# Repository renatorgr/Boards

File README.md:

# Boards

Hardware and firmware for the AgOpenGPS **AiO v4.5** autosteer boards (Micro and Standard), plus section controllers for a field sprayer and a no-till seed drill. Everything here works with [AgOpenWeb](https://github.com/AgOpenGPS-Official/AgOpenWeb) and [AgOpenGPS](https://github.com/AgOpenGPS-Official/AgOpenGPS).

> [!WARNING]
> This firmware steers a tractor. Test every new version on the bench before you use it in the field. It comes with no warranty.

## What's inside

| Folder | What it is |
|---|---|
| [`Firmware/v4.5_AiO_WEB`](Firmware/v4.5_AiO_WEB) | Teensy 4.1 firmware for the AiO v4.5 Micro and Standard. Handles the GPS (UM982, F9P, X20P or dual F9P), the IMU (TM171 or BNO085) and autosteer (Cytron, IBT2, Danfoss or Keya). Has its own web page for status, settings and firmware updates over the network. |
| [`Firmware/v4.5_AiO_WEB/v4.5_XIAO_ESP32`](Firmware/v4.5_AiO_WEB/v4.5_XIAO_ESP32) | Program for a Seeed XIAO ESP32C3 or ESP32S3 on the GPS2 port. The XIAO runs its own Wi-Fi network, so you can check the module from your phone without the tablet. |
| [`Firmware/v4.5_AiO_WEB/v4.5_XIAO_ESP32_bin`](Firmware/v4.5_AiO_WEB/v4.5_XIAO_ESP32_bin) | The XIAO program, compiled and ready to install. |
| [`Firmware/simulator`](Firmware/simulator) | The web pages of the Teensy, the XIAO and the ESP32 seed drill and sprayer modules with pretend boards behind them, to try online without a board: **[renatorgr.github.io/Boards](https://renatorgr.github.io/Boards/)**. Rebuilt from the code on every change. |
| [`AiO_Micro45_XIAO_C3`](AiO_Micro45_XIAO_C3) | Adapter board (KiCad) that plugs a XIAO into the GPS2 socket of the AiO v4.5 Micro. Gerber, BOM and CPL files are ready to order from JLCPCB. |
| [`AiO_Std45_XIAO_C3`](AiO_Std45_XIAO_C3) | The same adapter for the AiO v4.5 Standard. |
| [`LED_Bezel`](LED_Bezel) | A small 3D-printed comb (OpenSCAD and STL) that slides over the three front LEDs of the AiO v4.5 so each one lights only its own window on the panel. |
| [`Relay24_ESP32`](Relay24_ESP32) | Relay board (KiCad) for an ESP32 DevKitC: 24 DPDT relays that drive 12 V linear actuators in both directions, a network socket and 12 V in, for the seed drill's sections. Gerber, BOM and CPL files for JLCPCB. |
| [`Seeder/Seeder_ESP32`](Seeder/Seeder_ESP32) | Program for the Relay24_ESP32 board (or a KinCony KC868-A32: ESP32, 32 relays, network cable) that runs the 19 sections of the no-till seed drill, one linear actuator each, on command from AgOpenWeb or AgOpenGPS (the official machine-module messages, PGN 229 for sections 17–64). Has its own web page for setup and updates. |
| [`Sprayer/Sprayer_ESP32`](Sprayer/Sprayer_ESP32) | Program for an ESP32 relay board (the ESP32_Relay_X8, or a plain ESP32 with relay modules, up to 16 relays) that runs the sprayer sections over Wi-Fi. Opens and closes the section valves on command from AgOpenWeb or AgOpenGPS (the official machine-module messages), reports boom pressure and flow, and has its own web page for setup and updates. |
| [`Sprayer/Sprayer_Nano`](Sprayer/Sprayer_Nano) | The earlier Arduino Nano + Ethernet version of the same sprayer controller. |

Each folder has its own README with the details.

## Status

- **Teensy firmware v4.5:** runs on the bench with a UM982, F9P or X20P and a TM171 or BNO085. The dual F9P, the Keya motor and steering with a BNO085 have not been tried on a tractor yet.
- **XIAO program v4.5:** must match the Teensy firmware version.
- **Adapter boards and Relay24_ESP32:** designed and checked in KiCad, but not built or tested yet.
- **Sprayer ESP32 v0.9:** runs on the bench (page, Wi-Fi), not tested on the sprayer yet. Also builds for a plain ESP32 with relay modules (up to 16 relays). Sensor dividers use 10 kΩ and 22 kΩ resistors from a common kit. The sensors fitted are ticked on its page: with none it sends no PGN 160. The Nano version (v0.3) is kept as it was.
- **Seeder ESP32 v0.2:** the seed drill part of Sprayer ESP32 v0.8 in its own folder: 19 sections over the network cable, relay 1 = section 1 and so on, on the Relay24_ESP32 board (default) or a KC868-A32. Written from the board design and KinCony's pin list, not yet run on a board.

## Getting started

### Teensy firmware

1. **First install:** connect the Teensy over USB, open the `.hex` file from [`Firmware/v4.5_AiO_WEB`](Firmware/v4.5_AiO_WEB) in Teensy Loader, then press the button on the Teensy.
2. **Web page:** open `http://192.168.5.126/` (or `http://aio.local/`) in a browser on the same network. The third number follows the subnet set in AgOpenWeb; it can also be changed from the XIAO's WiFi page (WiFi tab → Module network). To see the page before you have a module: the [simulator](https://renatorgr.github.io/Boards/).
3. **Updates:** on the web page, go to **Firmware** and choose a new `.hex` file, or click **Install from GitHub**. The page checks this repository for new versions.

### XIAO

1. **First install:** over USB-C, using the `…_USB.bin` file for your XIAO and the [esptool-js](https://espressif.github.io/esptool-js/) web page. Step-by-step instructions are in the [`v4.5_XIAO_ESP32_bin` README](Firmware/v4.5_AiO_WEB/v4.5_XIAO_ESP32_bin).
2. Join the `XIAO-xxxx` Wi-Fi network (password `agopengps`) and open `http://192.168.4.1/`.
3. **Updates:** over Wi-Fi from the XIAO page.

### Seed drill

Choosing the board, wiring (actuators, end switches), the first upload, the setup and a bench test are in the [`Seeder_ESP32` README](Seeder/Seeder_ESP32). Its web page can be tried without the board in the [simulator](https://renatorgr.github.io/Boards/seeder/).

### Sprayer

Wiring, the first upload, the Wi-Fi setup and a bench test are in the [`Sprayer_ESP32` README](Sprayer/Sprayer_ESP32). Its web page can be tried without the board in the [simulator](https://renatorgr.github.io/Boards/sprayer/). The pressure, flow and alarms show in the [AgOpenWeb fork with the sprayer readout](https://github.com/renatorgr/AgOpenWeb). The older Nano version is in [`Sprayer_Nano`](Sprayer/Sprayer_Nano).

## Building from source

- Arduino IDE 1.8 or 2.x with **Teensyduino 1.58**.
- Board settings: Teensy 4.1, USB Type "Serial", CPU Speed 600 MHz, Optimize "Faster".
- No extra libraries needed: everything the sketch uses is in its folder or comes with Teensyduino.
- GitHub Actions compiles the Teensy firmware on every pull request. A green check means it builds. The `.hex` file is under **Artifacts** on the run's page.

## Credits and licence

This work builds on the AgOpenGPS project and its community. The full list of credits is in the [Teensy firmware README](Firmware/v4.5_AiO_WEB/README.md#credits-and-licence).

- **Teensy and XIAO firmware:** GNU General Public License v3 or later. See [`COPYING`](Firmware/v4.5_AiO_WEB/COPYING).
- **Adapter boards:** same licence as the AgOpenGPS boards they fit.

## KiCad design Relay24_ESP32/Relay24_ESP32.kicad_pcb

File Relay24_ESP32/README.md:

# Relay24_ESP32 - 24-section relay board for an ESP32 DevKitC

A 210 x 120 mm two-layer board that holds everything needed to drive 24 sections with
12 V linear actuators from AgOpenGPS / AgOpenWeb (machine module over UDP):

- an **ESP32 DevKitC V4** (38 pins) plugged into two 1x19 sockets, running
  [Seeder_ESP32](../Seeder/Seeder_ESP32) or [Sprayer_ESP32](../Sprayer/Sprayer_ESP32)
  with a board profile for this hardware (see *Firmware* below);
- **three 74HC595 shift registers + three ULN2803A** driving **24 DPDT relays**
  (HF115F/012-2ZS4, 8 A); each relay reverses one actuator: relay off = actuator pulled
  in (section closed), relay on = actuator pushed out (section open); a green LED per
  section;
- **RTL8201F + RJ45** (RMII; the PHY runs on its own 25 MHz crystal and feeds the 50 MHz
  reference clock into GPIO0) so the module can sit on the tractor network cable; Wi-Fi
  stays available;
- **12 V in** with reverse-polarity diode, TVS and bulk capacitor, **LM2596S-5.0 buck**
  to 5 V (DevKitC) and **AMS1117-3.3** for the logic and the PHY;
- the actuator power comes in on its **own terminals**, one pair of rails per relay row,
  so the 12 V for the actuators never flows through the logic supply.

Schematic: [Relay24_ESP32_schematic.pdf](Relay24_ESP32_schematic.pdf). Bottom view:
[pcb_bottom.png](pcb_bottom.png). The design has **not been built yet**; see *Before
ordering* at the end.

## Connections

All screw terminals are 5.08 mm KF301 blocks, wire openings towards the board edge.

| Terminal | Function |
|---|---|
| J1 .. J12 (top edge) | sections 1 .. 12, pin 1 = red wire, pin 2 = black wire of the actuator |
| J13 .. J24 (bottom edge) | sections 13 .. 24 (13 is under 12, 24 under 1) |
| J26, J27 (top edge, both ends) | 12 V ACT A: + and - of the actuator supply for sections 1-12 (feed from one end or both) |
| J28, J29 (bottom edge, both ends) | 12 V ACT B: same for sections 13-24 |
| J25 (right edge) | 12 V IN for the board and the relay coils (put a 2 A fuse in the wire) |
| J32 | RJ45, 100 Mbit, with magnetics and link / speed LEDs on the board |
| J33 | I2C header: 3V3, GND, SDA (GPIO15), SCL (GPIO14), with 4.7 k pull-ups |
| J34 | analog header: 3V3, GND, GPIO34, GPIO35 (0 - 3.3 V inputs) |

All grounds are common (board 12 V, actuator rails, ESP32). The relay contacts:
common 1 -> red wire, common 2 -> black wire; with the coil off the red wire is on GND
and the black wire on the actuator rail, with the coil on it is the other way round.
Swap the two wires of an actuator if it moves the wrong way.

## ESP32 pins

| Function | GPIO | Notes |
|---|---|---|
| 74HC595 data (SER) | 13 | three registers in a chain: U1 (sections 1-8) -> U2 (9-16) -> U3 (17-24) |
| 74HC595 clock (SRCLK) | 16 | |
| 74HC595 latch (RCLK) | 32 | |
| 74HC595 output enable (OE, active low) | 4 | 4.7 k pull-up: all relays off until the program drives it low |
| RTL8201F MDC / MDIO | 23 / 18 | PHY address 0 (strap resistors R32 / R36) |
| RMII TXD0 / TXD1 / TX_EN | 19 / 22 / 21 | |
| RMII RXD0 / RXD1 / CRS_DV | 25 / 26 / 27 | |
| RMII 50 MHz clock | 0 | input from the PHY (`ETH_CLOCK_GPIO0_IN`), 33 ohm series resistor; quiet at boot because the PHY is in reset |
| PHY reset / power | 33 | 10 k pull-down: the PHY stays in reset until the program sets it high |
| I2C | 15 (SDA), 14 (SCL) | header J33 |
| Analog | 34, 35 | header J34, input only |

Pins 2, 5, 12 and 17 are left free. GPIO0 carries the Ethernet clock, but only once the
program releases the PHY reset on GPIO33, so the DevKitC still boots and flashes normally
(GPIO0 is the only pin the ESP32 accepts the clock on).

## Firmware

[Seeder_ESP32](../Seeder/Seeder_ESP32) v0.2 runs this board (`BOARD_RELAY24`, its
default):

- sections through the 74HC595 chain (bit 0 = section 1): 24 bits on GPIO13 / GPIO16,
  relay 24 first, latch on GPIO32; GPIO4 goes low only after the chips hold zeros;
- Ethernet: `ETH.begin(ETH_PHY_RTL8201, 0, 23, 18, 33, ETH_CLOCK_GPIO0_IN)` with
  arduino-esp32 3.x (in 2.x the order is `ETH.begin(0, 33, 23, 18, ETH_PHY_RTL8201,
  ETH_CLOCK_GPIO0_IN)`); the driver lets the PHY out of reset before it starts the
  ESP32's network block, which needs the clock. Before a restart the program puts the
  PHY back in reset;
- the DevKitC's BOOT button is not read while the network cable is in use (GPIO0 carries
  the clock); `wifi-reset` on the Serial Monitor resets a forgotten Wi-Fi password;
- the LEDs next to the relays and the PHY LEDs need no code: D30 (yellow) lights for a
  10 Mbit link, D31 (green) for 100 Mbit, the chip's default LED mode (a program can
  change it through MDIO, page 7 register 19).

## Power

- 12 V IN: board logic + relay coils, about 0.1 A idle, up to 1.1 A with all 24 coils
  on (33 mA each). Reverse-polarity diode, 18 V TVS, 100 uF.
- Actuator rails: one 12 V feed per row of 12 relays; the copper rail is 9 mm wide on
  the top layer with a second strip on the bottom layer. Feed each rail from both ends
  (J26 + J27, J28 + J29) when several actuators may move at once, or order the board
  with 2 oz copper.
- The DevKitC can be powered from USB for programming on the bench: D28 keeps the USB
  5 V out of the buck converter.

## Files

- `Relay24_ESP32.kicad_pro`, `.kicad_sch` (+ three relay sheets), `.kicad_pcb`: KiCad 7
  project. `Relay24_ESP32_schematic.pdf`, `pcb_top.png`, `pcb_bottom.png`,
  `pcb_copper_*.png`: views.
- `fabrication_JLCPCB/`: `Gerber_Relay24_ESP32.zip` (Gerber + drill), `BOM_*_all.csv` /
  `CPL_*_all.csv` (every part) and `BOM_*_smd.csv` / `CPL_*_smd.csv` (surface-mount parts
  only, for an order where the relays, terminals, sockets and RJ45 are soldered by hand).
  JLCPCB format: BOM columns *Comment, Designator, Footprint, LCSC Part #*; CPL columns
  *Designator, Mid X, Mid Y, Layer, Rotation*.
- `tools/`: the generators. `design.py` holds every part, net and position;
  `make_sch.py` writes the schematic, `make_pcb.py` places and routes the board
  (`router.py` is a small grid router for the logic signals), `make_fab.py` writes the
  JLCPCB files and the views. Run them from the project folder with the Python of
  KiCad 7 (`python3 tools/make_pcb.py .`).

## Before ordering

Things that were assumed and should be checked on the real parts:

- The DevKitC V4 sockets are 25.4 mm apart (38-pin module). Measure your module; the
  30-pin DevKitC has another pitch and does not fit.
- The RJ45 is the HanRun HR911105A pinout (pairs on 1-2 and 3-6, centre taps 4-5 and
  7-8 to 3.3 V); another jack with built-in magnetics may differ. The PHY transmit pair
  pair (MDI pair 0) is wired to pins 1-2 and the receive pair (MDI pair 1) to pins 3-6,
  the usual wiring of an end device; the RTL8201F Auto-MDIX sorts out a crossed cable.
- The RTL8201F replaced the LAN8720A on 2026-10-28 because JLCPCB assembles the LAN8720A
  only on its Standard service (setup fee, wider board). The PHY runs on a 25 MHz crystal
  and sends the reference clock out; the ESP32 reads it on GPIO0. Nothing of this has
  been built yet.
- Y1 is a 5.0 x 3.2 mm two-pin crystal (YXC X503225MSB2GI, load capacitance 20 pF, with
  33 pF from each pin to ground). JLCPCB flags the smaller 3.2 x 2.5 mm four-pin crystal
  as hard to assemble and may charge extra for it, so do not swap it back.
- The screw terminals follow the KiCad `TerminalBlock_bornier-2_P5.08mm` footprint
  (wire opening on the pin-2 side); check the orientation on the first board.
- LCSC numbers were checked against the JLCPCB parts pages on 2026-10-28; stock
  changes, so a part shown as short at order time needs an equivalent with the same
  footprint. Second-source choices: the ULN2803 is Shanghai Belling (C22437476, same
  pinout as the TI ULN2803A), the LEDs are XINGLIGHT (the "green" ones are yellow-green,
  Vf 2.2 V, low enough for the Ethernet LEDs on 3.3 V).
- L1 is the SHOU HAN CYH127-33UH (12.3 x 12.3 mm) on KiCad's `L_12x12mm_H8mm` footprint
  (pads 2.9 x 5.4 mm, 9.9 mm apart): compare with the land pattern in its datasheet.
- The references of the resistors, capacitors and LEDs are not printed on the board
  (there is no room next to the PHY); the CPL files and the schematic have them.
- The CPL gives the centre of the body for the through-hole parts (relays, terminals,
  sockets, RJ45), as JLCPCB expects, and turns the 2.54 mm sockets and headers by 90
  degrees to match JLCPCB's models. The other rotations are KiCad's; check the JLCPCB
  preview, in particular the diodes, the electrolytic capacitors, the TO-263 regulator,
  the SOT-223 and the QFN.
- Linear actuators often draw 2-3 A while moving: size the actuator supply and the fuse
  accordingly.

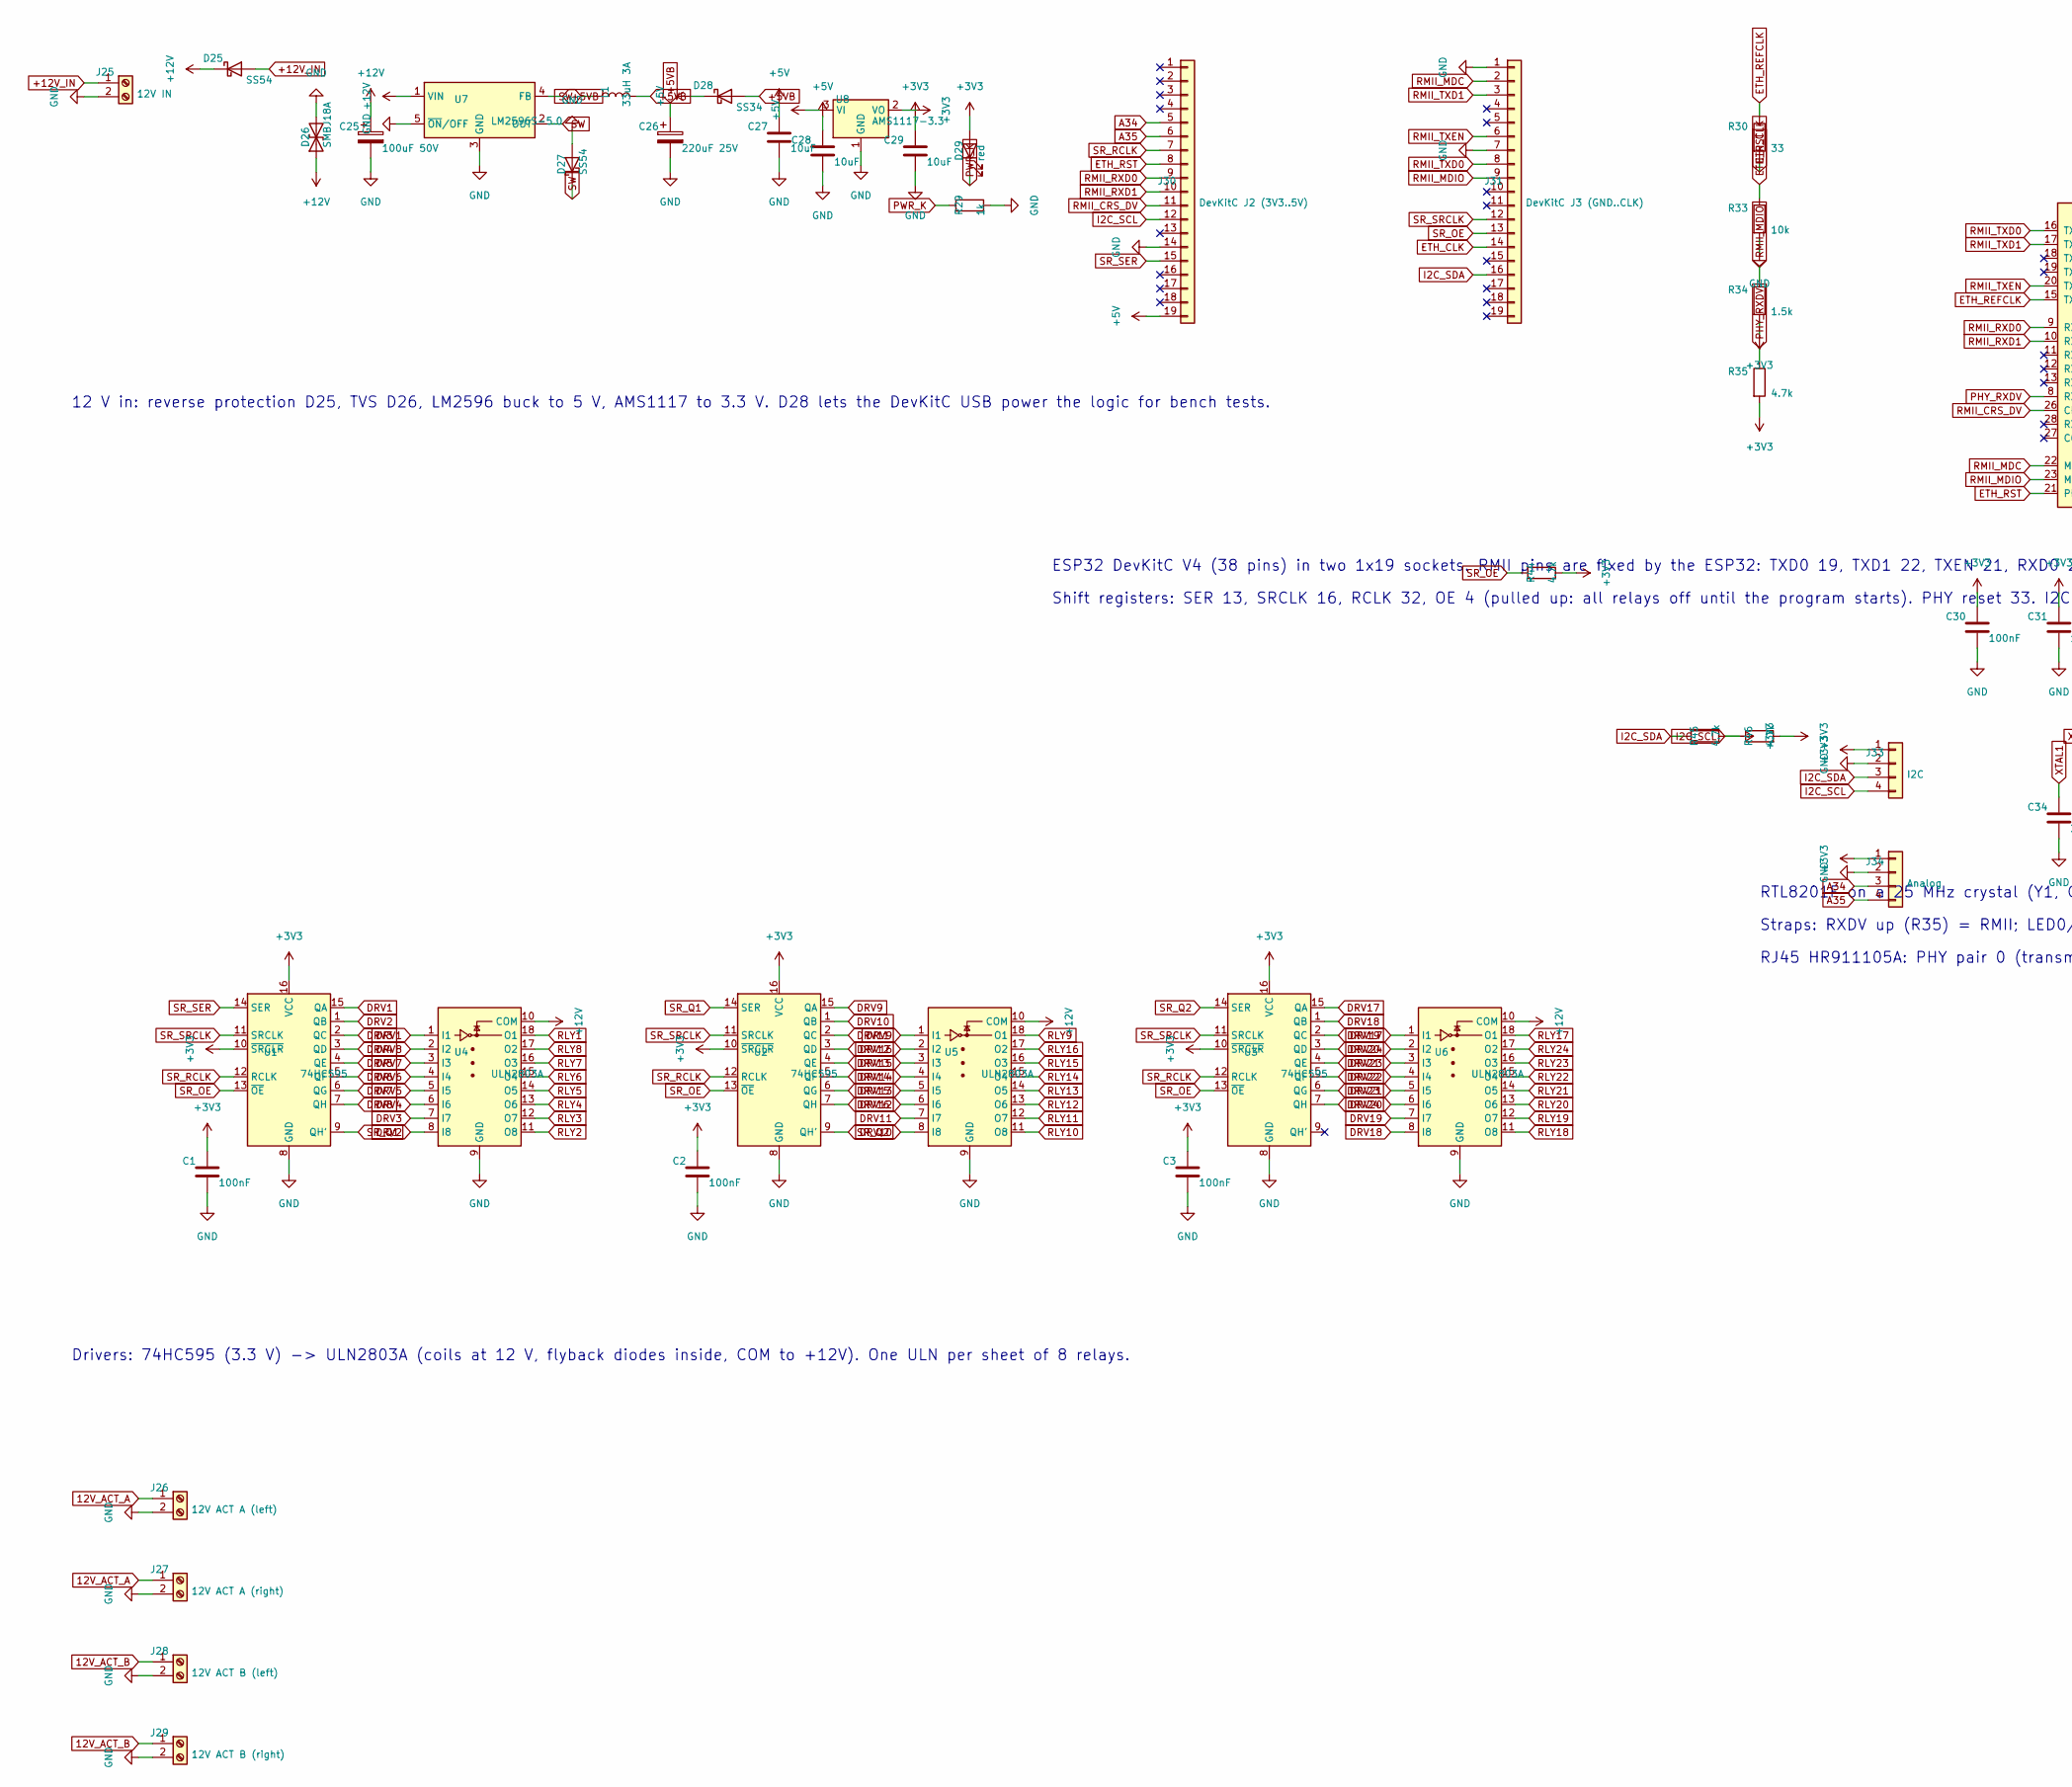
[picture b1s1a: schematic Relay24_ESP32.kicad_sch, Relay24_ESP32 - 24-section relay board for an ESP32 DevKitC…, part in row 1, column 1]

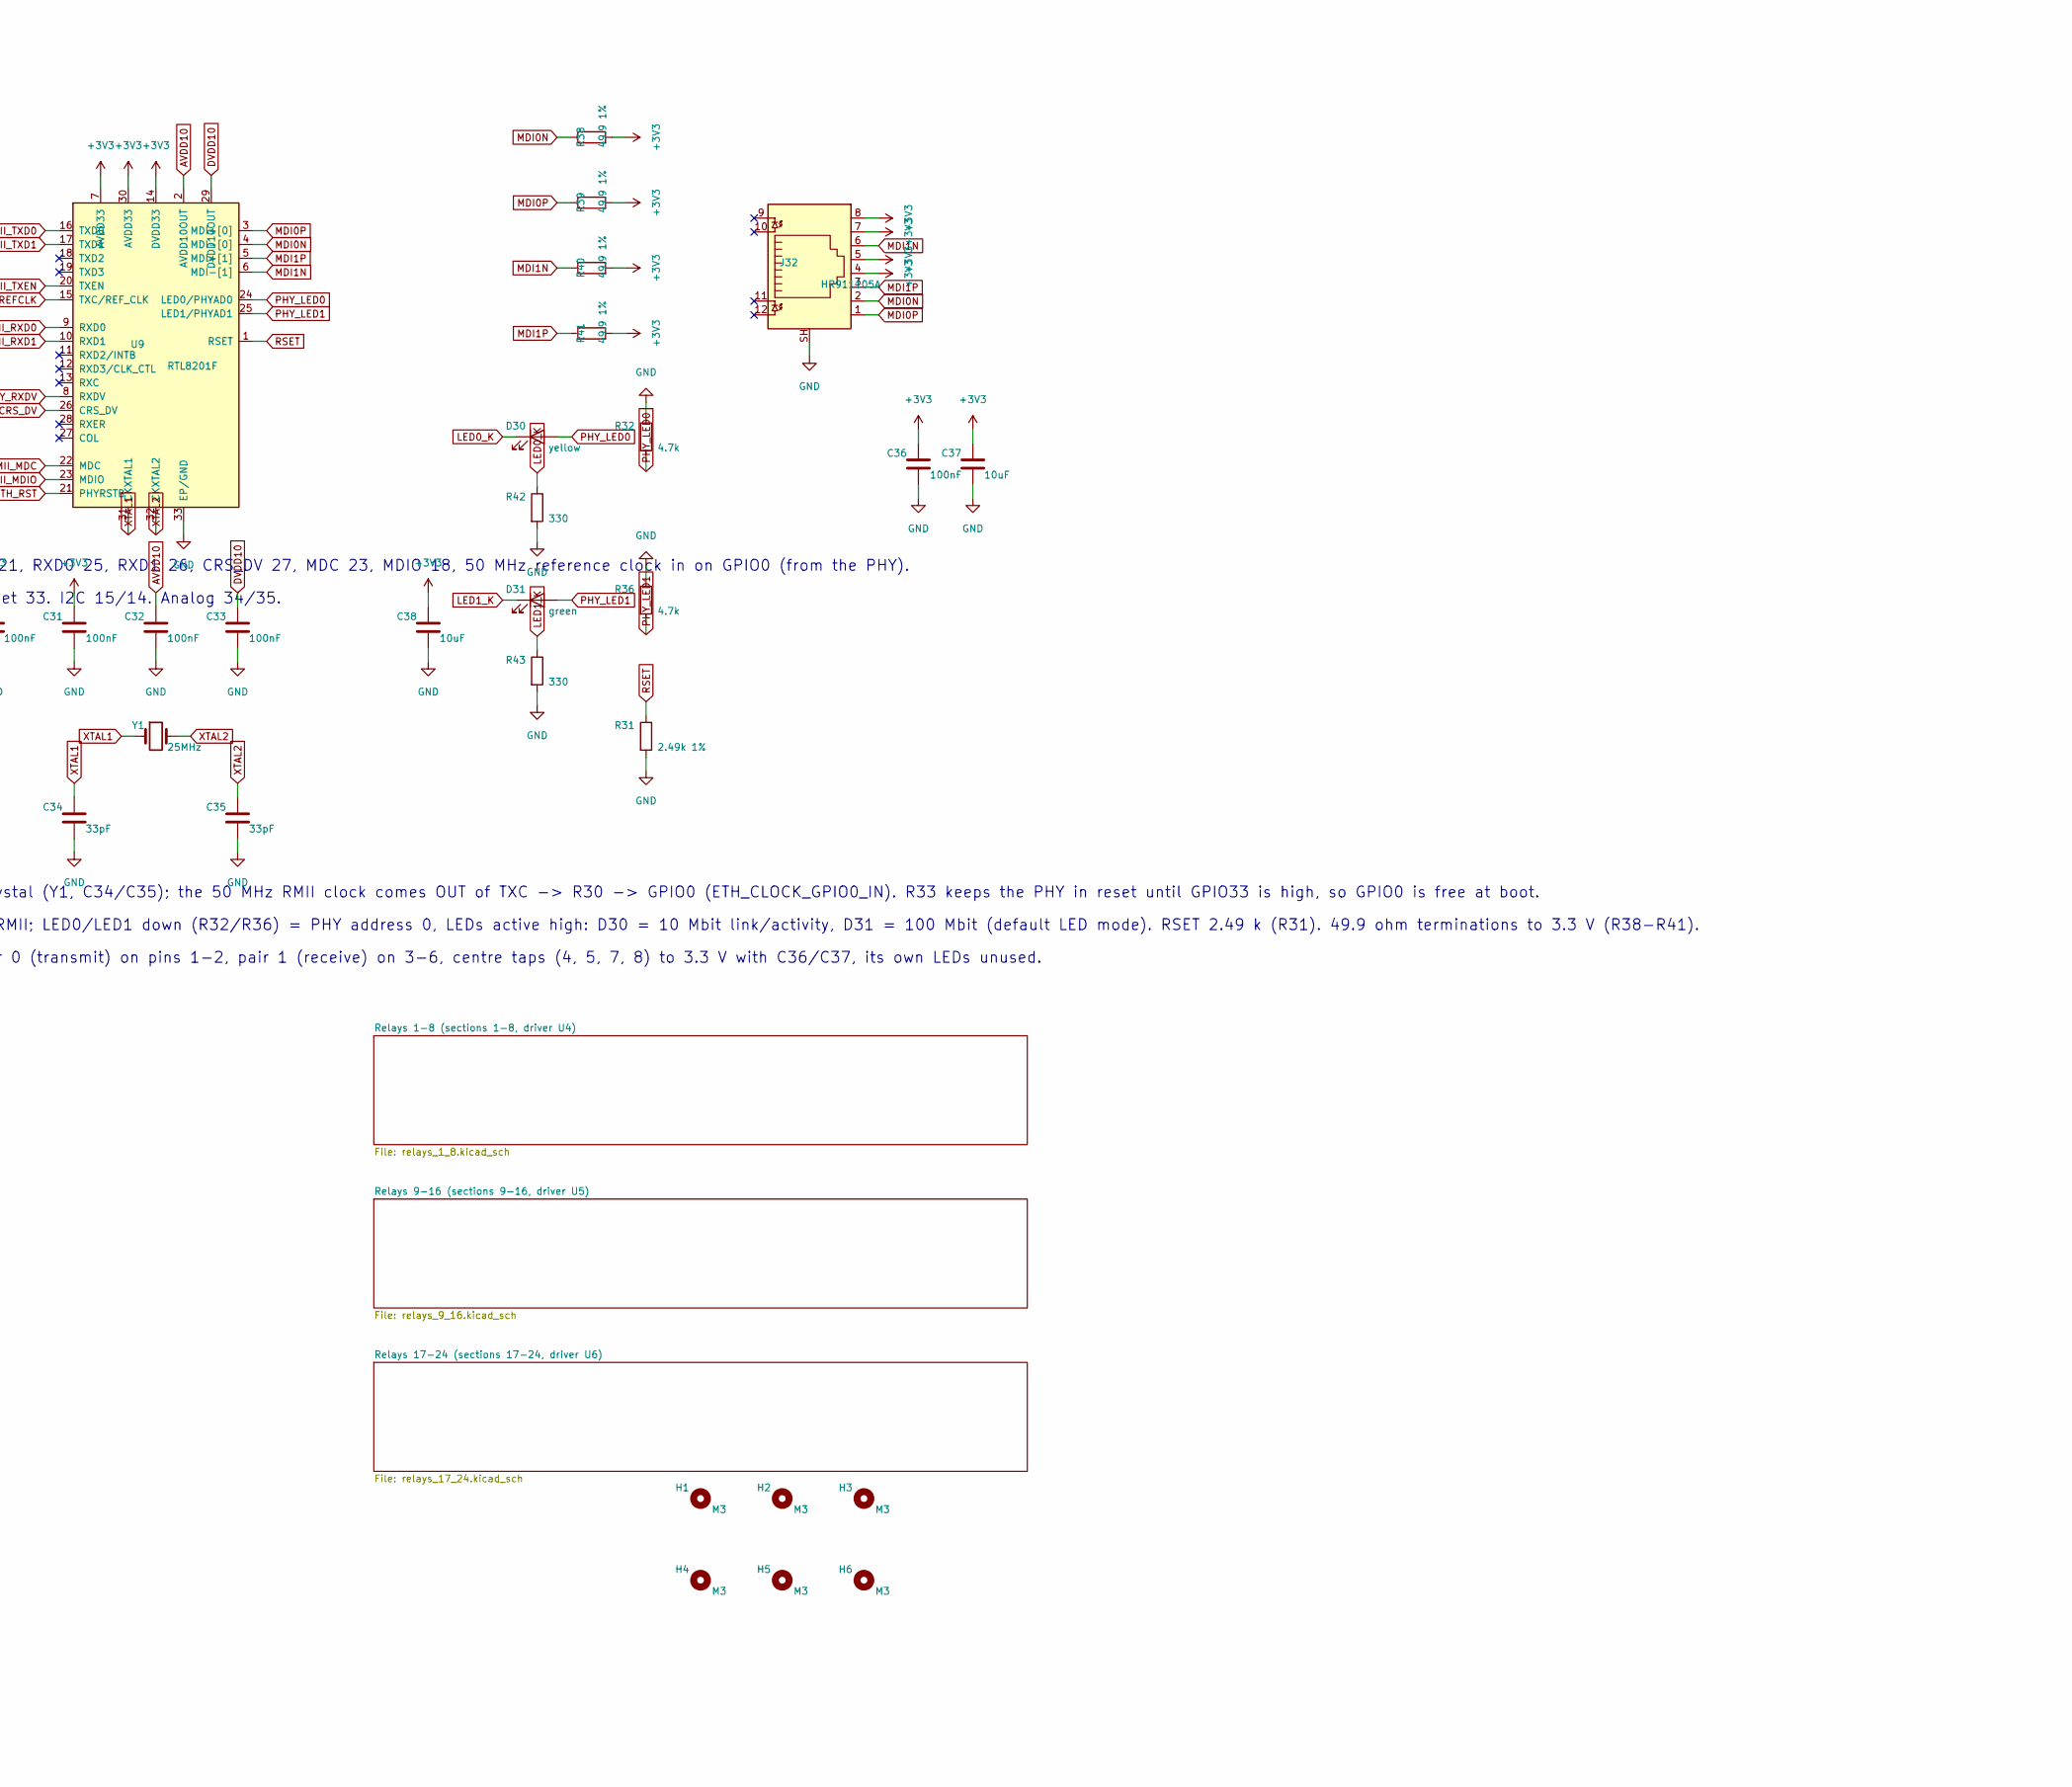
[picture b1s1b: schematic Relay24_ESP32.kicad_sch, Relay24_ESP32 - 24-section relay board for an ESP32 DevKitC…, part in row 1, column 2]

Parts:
C1, C2, C3, C30, C31, C32, C33, C36: 100nF; C_0603_1608Metric; LCSC C14663
C25: 100uF 50V; CP_Elec_8x10; LCSC C97812
C26: 220uF 25V; CP_Elec_8x10; LCSC C165536
C27, C28, C29, C37, C38: 10uF; C_0805_2012Metric; LCSC C15850
C34, C35: 33pF; C_0603_1608Metric; LCSC C1663
D25, D27: SS54; D_SMA; LCSC C22452
D26: SMBJ18A; D_SMB; LCSC C151256
D28: SS34; D_SMA; LCSC C8678
D29: red; LED_0603_1608Metric; LCSC C2286
D30: yellow; LED_0603_1608Metric; LCSC C965802
D31: green; LED_0603_1608Metric; LCSC C965805
H1, H2, H3, H4, H5, H6: M3; MountingHole_3.2mm_M3
J25: 12V IN; TerminalBlock_bornier-2_P5.08mm; LCSC C8465
J26: 12V ACT A (left); TerminalBlock_bornier-2_P5.08mm; LCSC C8465
J27: 12V ACT A (right); TerminalBlock_bornier-2_P5.08mm; LCSC C8465
J28: 12V ACT B (left); TerminalBlock_bornier-2_P5.08mm; LCSC C8465
J29: 12V ACT B (right); TerminalBlock_bornier-2_P5.08mm; LCSC C8465
J30: DevKitC J2 (3V3..5V); PinSocket_1x19_P2.54mm_Vertical; LCSC C319202
J31: DevKitC J3 (GND..CLK); PinSocket_1x19_P2.54mm_Vertical; LCSC C319202
J32: HR911105A; RJ45_Hanrun_HR911105A_Horizontal; LCSC C12074
J33: I2C; PinHeader_1x04_P2.54mm_Vertical; LCSC C124378
J34: Analog; PinHeader_1x04_P2.54mm_Vertical; LCSC C124378
L1: 33uH 3A; L_12x12mm_H8mm; LCSC C2929502
R29: 1k; R_0603_1608Metric; LCSC C21190
R30: 33; R_0603_1608Metric; LCSC C23140
R31: 2.49k 1%; R_0603_1608Metric; LCSC C136931
R32, R35, R36, R44, R45, R46: 4.7k; R_0603_1608Metric; LCSC C23162
R33: 10k; R_0603_1608Metric; LCSC C25804
R34: 1.5k; R_0603_1608Metric; LCSC C22843
R38, R39, R40, R41: 49.9 1%; R_0603_1608Metric; LCSC C23185
R42, R43: 330; R_0603_1608Metric; LCSC C23138
U1, U2, U3: 74HC595; SOIC-16_3.9x9.9mm_P1.27mm; LCSC C5947
U4, U5, U6: ULN2803A; SOIC-18W_7.5x11.6mm_P1.27mm; LCSC C22437476
U7: LM2596S-5.0; TO-263-5_TabPin3; LCSC C347421
U8: AMS1117-3.3; SOT-223-3_TabPin2; LCSC C6186
U9: RTL8201F; QFN-32-1EP_5x5mm_P0.5mm_EP3.45x3.45mm_ThermalVias; LCSC C45044
Y1: 25MHz; Crystal_SMD_5032-2Pin_5.0x3.2mm; LCSC C112569

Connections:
12V_ACT_A: J26.1, J27.1; also elsewhere on the board
12V_ACT_B: J28.1, J29.1; also elsewhere on the board
+3V3: C1.1, C2.1, C3.1, C29.1, C30.1, C31.1, C36.1, C37.1, C38.1, D29.2 (A), J32.4, J32.5, J32.7, J32.8, J33.1, J34.1, R34.2, R35.2, R38.2, R39.2, R40.2, R41.2, R44.2, R45.2, R46.2, U1.10 (~SRCLR), U1.16 (VCC), U2.10 (~SRCLR), U2.16 (VCC), U3.10 (~SRCLR), U3.16 (VCC), U8.2 (VO), U9.7 (AVDD33), U9.14 (DVDD33), U9.30 (AVDD33)
+5V: C27.1, C28.1, D28.1 (K), J30.19, U8.3 (VI)
+5VB: C26.1, D28.2 (A), L1.2, U7.4 (FB)
+12V: C25.1, D25.1 (K), D26.1 (A1), U4.10 (COM), U5.10 (COM), U6.10 (COM), U7.1 (VIN); also elsewhere on the board
+12V_IN: D25.2 (A), J25.1
A34: J30.5, J34.3
A35: J30.6, J34.4
AVDD10: C32.1, U9.2 (AVDD10OUT)
DRV1: U1.15 (QA), U4.1 (I1)
DRV2: U1.1 (QB), U4.8 (I8)
DRV3: U1.2 (QC), U4.7 (I7)
DRV4: U1.3 (QD), U4.6 (I6)
DRV5: U1.4 (QE), U4.5 (I5)
DRV6: U1.5 (QF), U4.4 (I4)
DRV7: U1.6 (QG), U4.3 (I3)
DRV8: U1.7 (QH), U4.2 (I2)
DRV9: U2.15 (QA), U5.1 (I1)
DRV10: U2.1 (QB), U5.8 (I8)
DRV11: U2.2 (QC), U5.7 (I7)
DRV12: U2.3 (QD), U5.6 (I6)
DRV13: U2.4 (QE), U5.5 (I5)
DRV14: U2.5 (QF), U5.4 (I4)
DRV15: U2.6 (QG), U5.3 (I3)
DRV16: U2.7 (QH), U5.2 (I2)
DRV17: U3.15 (QA), U6.1 (I1)
DRV18: U3.1 (QB), U6.8 (I8)
DRV19: U3.2 (QC), U6.7 (I7)
DRV20: U3.3 (QD), U6.6 (I6)
DRV21: U3.4 (QE), U6.5 (I5)
DRV22: U3.5 (QF), U6.4 (I4)
DRV23: U3.6 (QG), U6.3 (I3)
DRV24: U3.7 (QH), U6.2 (I2)
DVDD10: C33.1, U9.29 (DVDD10OUT)
ETH_CLK: J31.14, R30.2
ETH_REFCLK: R30.1, U9.15 (TXC/REF_CLK)
ETH_RST: J30.8, R33.1, U9.21 (PHYRSTB)
GND: C1.2, C2.2, C3.2, C25.2, C26.2, C27.2, C28.2, C29.2, C30.2, C31.2, C32.2, C33.2, C34.2, C35.2, C36.2, C37.2, C38.2, D26.2 (A2), D27.2 (A), J25.2, J26.2, J27.2, J28.2, J29.2, J30.14, J31.1, J31.7, J32.SH, J33.2, J34.2, R29.2, R31.2, R32.1, R33.2, R36.1, R42.2, R43.2, U1.8 (GND), U2.8 (GND), U3.8 (GND), U4.9 (GND), U5.9 (GND), U6.9 (GND), U7.3 (GND), U7.5 (~ON/OFF), U8.1 (GND), U9.33 (EP/GND); also elsewhere on the board
I2C_SCL: J30.12, J33.4, R46.1
I2C_SDA: J31.16, J33.3, R45.1
LED0_K: D30.1 (K), R42.1
LED1_K: D31.1 (K), R43.1
MDI0N: J32.2, R38.1, U9.4 (MDI-[0])
MDI0P: J32.1, R39.1, U9.3 (MDI+[0])
MDI1N: J32.6, R40.1, U9.6 (MDI-[1])
MDI1P: J32.3, R41.1, U9.5 (MDI+[1])
PHY_LED0: D30.2 (A), R32.2, U9.24 (LED0/PHYAD0)
PHY_LED1: D31.2 (A), R36.2, U9.25 (LED1/PHYAD1)
PHY_RXDV: R35.1, U9.8 (RXDV)
PWR_K: D29.1 (K), R29.1
RLY1: U4.18 (O1); also elsewhere on the board
RLY2: U4.11 (O8); also elsewhere on the board
RLY3: U4.12 (O7); also elsewhere on the board
RLY4: U4.13 (O6); also elsewhere on the board
RLY5: U4.14 (O5); also elsewhere on the board
RLY6: U4.15 (O4); also elsewhere on the board
RLY7: U4.16 (O3); also elsewhere on the board
RLY8: U4.17 (O2); also elsewhere on the board
RLY9: U5.18 (O1); also elsewhere on the board
RLY10: U5.11 (O8); also elsewhere on the board
RLY11: U5.12 (O7); also elsewhere on the board
RLY12: U5.13 (O6); also elsewhere on the board
RLY13: U5.14 (O5); also elsewhere on the board
RLY14: U5.15 (O4); also elsewhere on the board
RLY15: U5.16 (O3); also elsewhere on the board
RLY16: U5.17 (O2); also elsewhere on the board
RLY17: U6.18 (O1); also elsewhere on the board
RLY18: U6.11 (O8); also elsewhere on the board
RLY19: U6.12 (O7); also elsewhere on the board
RLY20: U6.13 (O6); also elsewhere on the board
RLY21: U6.14 (O5); also elsewhere on the board
RLY22: U6.15 (O4); also elsewhere on the board
RLY23: U6.16 (O3); also elsewhere on the board
RLY24: U6.17 (O2); also elsewhere on the board
RMII_CRS_DV: J30.11, U9.26 (CRS_DV)
RMII_MDC: J31.2, U9.22 (MDC)
RMII_MDIO: J31.9, R34.1, U9.23 (MDIO)
RMII_RXD0: J30.9, U9.9 (RXD0)
RMII_RXD1: J30.10, U9.10 (RXD1)
RMII_TXD0: J31.8, U9.16 (TXD0)
RMII_TXD1: J31.3, U9.17 (TXD1)
RMII_TXEN: J31.6, U9.20 (TXEN)
RSET: R31.1, U9.1 (RSET)
SR_OE: J31.13, R44.1, U1.13 (~OE), U2.13 (~OE), U3.13 (~OE)
SR_Q1: U1.9 (QH'), U2.14 (SER)
SR_Q2: U2.9 (QH'), U3.14 (SER)
SR_RCLK: J30.7, U1.12 (RCLK), U2.12 (RCLK), U3.12 (RCLK)
SR_SER: J30.15, U1.14 (SER)
SR_SRCLK: J31.12, U1.11 (SRCLK), U2.11 (SRCLK), U3.11 (SRCLK)
SW: D27.1 (K), L1.1, U7.2 (OUT)
XTAL1: C34.1, U9.31 (CKXTAL1), Y1.1
XTAL2: C35.1, U9.32 (CKXTAL2), Y1.2

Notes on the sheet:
12 V in: reverse protection D25, TVS D26, LM2596 buck to 5 V, AMS1117 to 3.3 V. D28 lets the DevKitC USB power the logic for bench tests.
ESP32 DevKitC V4 (38 pins) in two 1x19 sockets. RMII pins are fixed by the ESP32: TXD0 19, TXD1 22, TXEN 21, RXD0 25, RXD1 26, CRS_DV 27, MDC 23, MDIO 18, 50 MHz reference clock in on GPIO0 (from the PHY).
Shift registers: SER 13, SRCLK 16, RCLK 32, OE 4 (pulled up: all relays off until the program starts). PHY reset 33. I2C 15/14. Analog 34/35.
RTL8201F on a 25 MHz crystal (Y1, C34/C35); the 50 MHz RMII clock comes OUT of TXC -> R30 -> GPIO0 (ETH_CLOCK_GPIO0_IN). R33 keeps the PHY in reset until GPIO33 is high, so GPIO0 is free at boot.
Straps: RXDV up (R35) = RMII; LED0/LED1 down (R32/R36) = PHY address 0, LEDs active high: D30 = 10 Mbit link/activity, D31 = 100 Mbit (default LED mode). RSET 2.49 k (R31). 49.9 ohm terminations to 3.3 V (R38-R41).
RJ45 HR911105A: PHY pair 0 (transmit) on pins 1-2, pair 1 (receive) on 3-6, centre taps (4, 5, 7, 8) to 3.3 V with C36/C37, its own LEDs unused.
Drivers: 74HC595 (3.3 V) -> ULN2803A (coils at 12 V, flyback diodes inside, COM to +12V). One ULN per sheet of 8 relays.

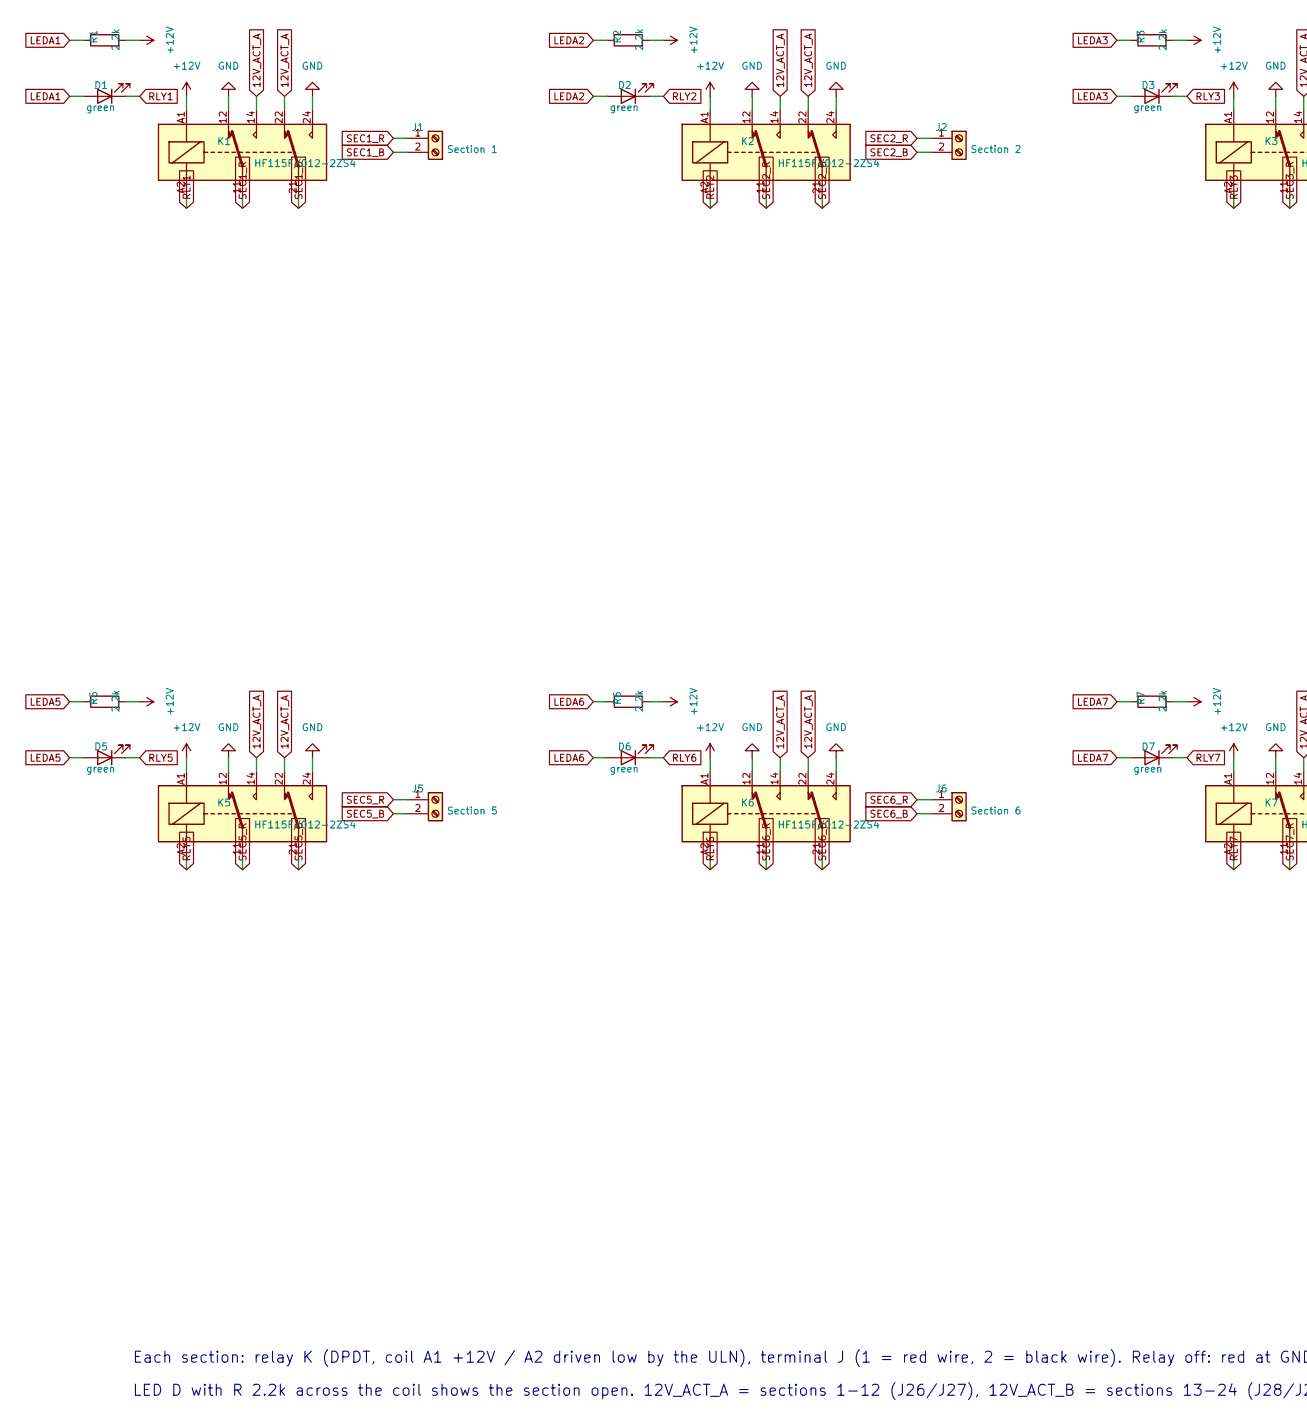
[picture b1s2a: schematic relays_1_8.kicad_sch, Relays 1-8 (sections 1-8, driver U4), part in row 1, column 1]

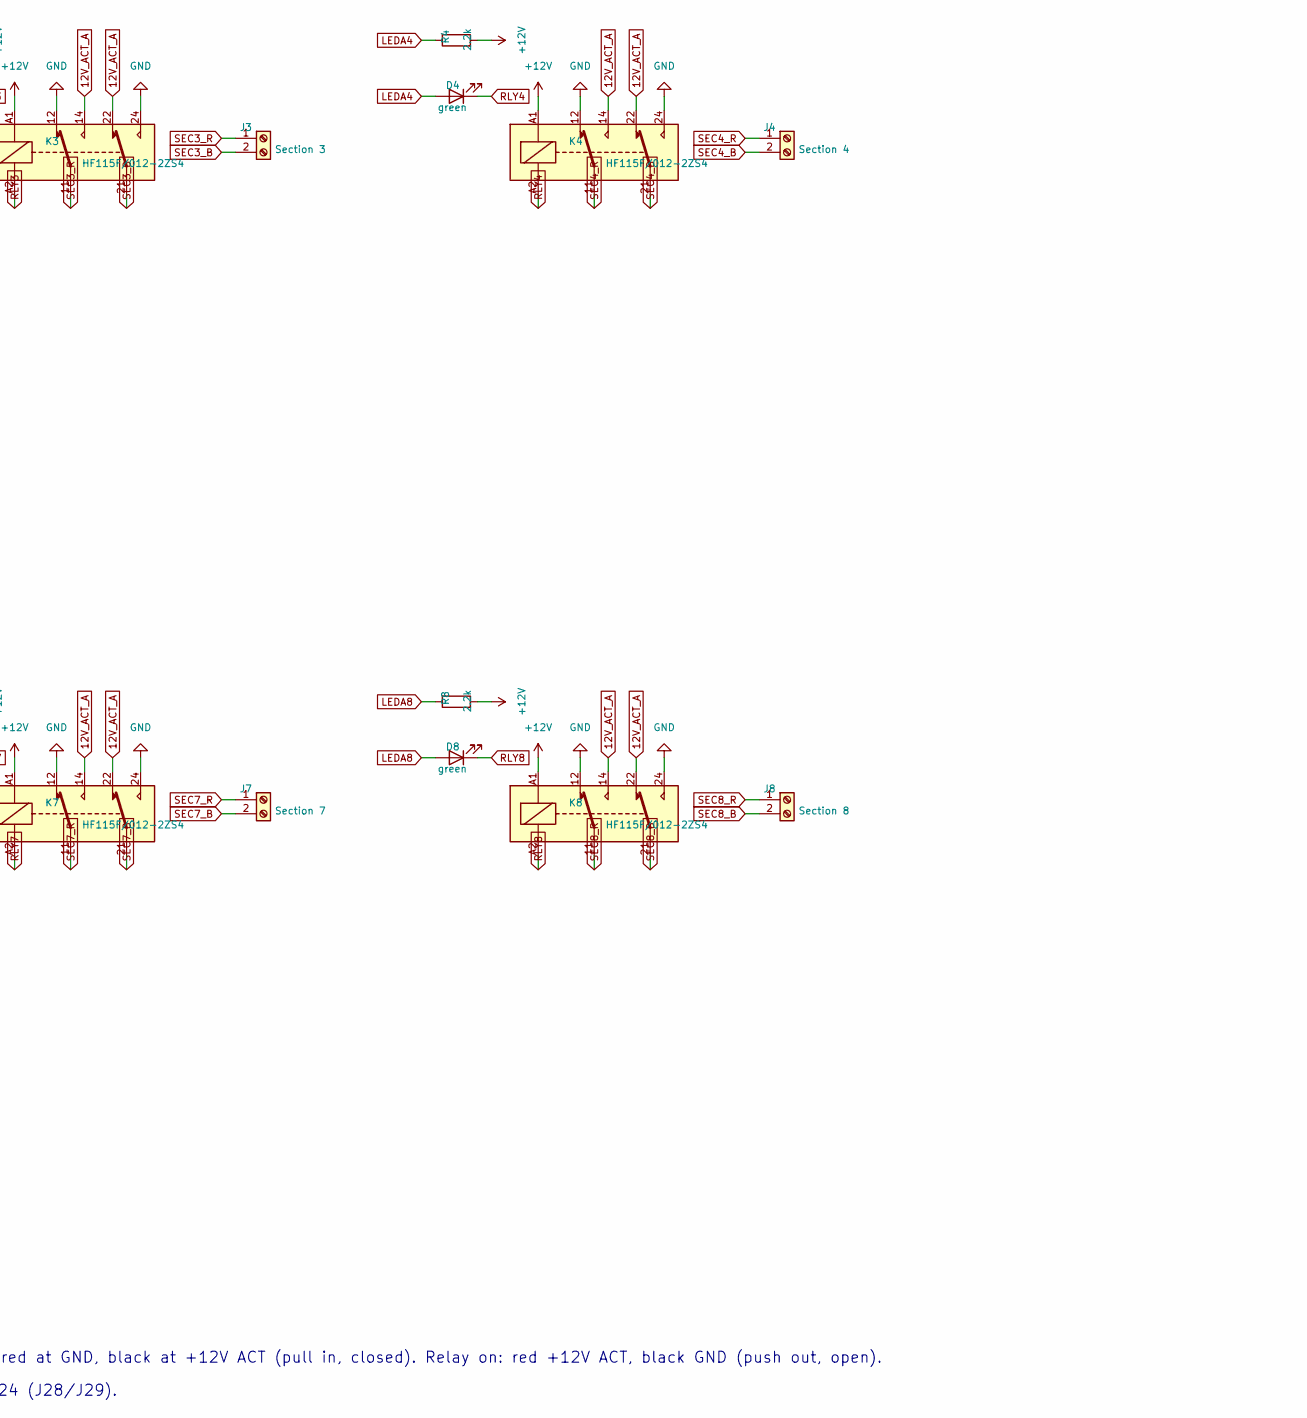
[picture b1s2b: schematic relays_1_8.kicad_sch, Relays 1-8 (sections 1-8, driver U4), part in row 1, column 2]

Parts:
D1, D2, D3, D4, D5, D6, D7, D8: green; LED_0603_1608Metric; LCSC C965805
J1: Section 1; TerminalBlock_bornier-2_P5.08mm; LCSC C8465
J2: Section 2; TerminalBlock_bornier-2_P5.08mm; LCSC C8465
J3: Section 3; TerminalBlock_bornier-2_P5.08mm; LCSC C8465
J4: Section 4; TerminalBlock_bornier-2_P5.08mm; LCSC C8465
J5: Section 5; TerminalBlock_bornier-2_P5.08mm; LCSC C8465
J6: Section 6; TerminalBlock_bornier-2_P5.08mm; LCSC C8465
J7: Section 7; TerminalBlock_bornier-2_P5.08mm; LCSC C8465
J8: Section 8; TerminalBlock_bornier-2_P5.08mm; LCSC C8465
K1, K2, K3, K4, K5, K6, K7, K8: HF115F/012-2ZS4; Relay_DPDT_Omron_G2RL-2; LCSC C163534
R1, R2, R3, R4, R5, R6, R7, R8: 2.2k; R_0603_1608Metric; LCSC C4190

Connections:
12V_ACT_A: K1.14, K1.22, K2.14, K2.22, K3.14, K3.22, K4.14, K4.22, K5.14, K5.22, K6.14, K6.22, K7.14, K7.22, K8.14, K8.22; also elsewhere on the board
+12V: K1.A1, K2.A1, K3.A1, K4.A1, K5.A1, K6.A1, K7.A1, K8.A1, R1.2, R2.2, R3.2, R4.2, R5.2, R6.2, R7.2, R8.2; also elsewhere on the board
GND: K1.12, K1.24, K2.12, K2.24, K3.12, K3.24, K4.12, K4.24, K5.12, K5.24, K6.12, K6.24, K7.12, K7.24, K8.12, K8.24; also elsewhere on the board
LEDA1: D1.2 (A), R1.1
LEDA2: D2.2 (A), R2.1
LEDA3: D3.2 (A), R3.1
LEDA4: D4.2 (A), R4.1
LEDA5: D5.2 (A), R5.1
LEDA6: D6.2 (A), R6.1
LEDA7: D7.2 (A), R7.1
LEDA8: D8.2 (A), R8.1
RLY1: D1.1 (K), K1.A2; also elsewhere on the board
RLY2: D2.1 (K), K2.A2; also elsewhere on the board
RLY3: D3.1 (K), K3.A2; also elsewhere on the board
RLY4: D4.1 (K), K4.A2; also elsewhere on the board
RLY5: D5.1 (K), K5.A2; also elsewhere on the board
RLY6: D6.1 (K), K6.A2; also elsewhere on the board
RLY7: D7.1 (K), K7.A2; also elsewhere on the board
RLY8: D8.1 (K), K8.A2; also elsewhere on the board
SEC1_B: J1.2, K1.21
SEC1_R: J1.1, K1.11
SEC2_B: J2.2, K2.21
SEC2_R: J2.1, K2.11
SEC3_B: J3.2, K3.21
SEC3_R: J3.1, K3.11
SEC4_B: J4.2, K4.21
SEC4_R: J4.1, K4.11
SEC5_B: J5.2, K5.21
SEC5_R: J5.1, K5.11
SEC6_B: J6.2, K6.21
SEC6_R: J6.1, K6.11
SEC7_B: J7.2, K7.21
SEC7_R: J7.1, K7.11
SEC8_B: J8.2, K8.21
SEC8_R: J8.1, K8.11

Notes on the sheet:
Each section: relay K (DPDT, coil A1 +12V / A2 driven low by the ULN), terminal J (1 = red wire, 2 = black wire). Relay off: red at GND, black at +12V ACT (pull in, closed). Relay on: red +12V ACT, black GND (push out, open).
LED D with R 2.2k across the coil shows the section open. 12V_ACT_A = sections 1-12 (J26/J27), 12V_ACT_B = sections 13-24 (J28/J29).

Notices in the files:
Relay24_ESP32/Relay24_ESP32.kicad_pcb:
Relay24_ESP32 v1.0  2026  renatorgr  GPL v3
Relay24_ESP32/Relay24_ESP32.kicad_sch:
Written by Claude (Anthropic) for renatorgr, GPL v3 or later
